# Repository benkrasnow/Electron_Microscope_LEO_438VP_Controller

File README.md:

# LEO 438VP control replacement: working files

Everything generated while reverse-engineering the LEO 438VP SEM's control system: the Win98 PC running LEO-32 plus the custom ISA image-processor board. The analysis tools read the original binaries from an image of the old PC's drive, which is not part of this repository.

Published at https://github.com/benkrasnow/Electron_Microscope_LEO_438VP_Controller. The capture data and the decompiled / disassembled text from the proprietary LEO-32 binaries are kept locally only (see `.gitignore`), so some files mentioned in the docs are not in the repository.

## Layout

| Folder | Contents |
|---|---|
| **`specifications/`** | **Start here: `LEO438VP_SYSTEM_DATASHEET.md` (summary of every subsystem and its architecture).** Detailed interface specs: `STAGE_VACUUM_INTERFACE_SPEC.md`, `VP_CONTROLLER_INTERFACE_SPEC.md`, `EHT_INTERFACE_SPEC.md`, `SCAN_GENERATOR_INTERFACE_SPEC.md` |
| `hardware/leo_control_box/` | KiCad 10 project for the Teensy 4.0 control box (schematic rev 0.1, PCB rev 0.1). See its README |
| **`firmware/`** | **Teensy 4.0 control-box firmware (`leo_control/`), the USB protocol for the PC page (`PROTOCOL.md`) and every runtime setting (`SETTINGS.md`). See `firmware/README.md`** |
| **`webui/`** | **Operator web page (Chrome / Edge): control box over Web Serial, OBI imaging through `bridge.py`, developer tools. See `webui/README.md`** |
| `design/` | Design notes, e.g. the Glasgow pin plan |
| `scope_tools/` | Tektronix MSO24 control and scan-fiber decoding scripts (`arm_burst.py`, `wait_grab_decode.sh`, `decode_scan_fiber.py`, …) and `SCAN_FIBER_NOTES.md` (working notes and test log) |
| `scope_captures/` | The annotated `scan_fiber_timing.png`. The scope captures themselves (`.npz` waveforms, `.png` screens, `_ch3.txt` decodes) are local only |
| `capture_tools/` | Live serial capture: Teensy 3.2 logger firmware, `capture_serial.py`, `decode_serial_log.py`, the protocol write-ups, and every capture. See `capture_tools/README.md`. |
| `capture_tools/captures/` | Raw logs (`<date>_<time>_<tag>.log`), operator notes, decoded timelines and CSVs (local only). |
| `capture_tools/teensy_blink_test/` | Blink sketch used to check the Teensy toolchain. |
| `report/` | The static-analysis report (`leo438vp_report.html`, also published as a claude.ai artifact) plus the section drafts and diagrams it was built from. |
| `analysis/` | Python tools for the original binaries, and their outputs (see below). |
| `notes/` | `PERFORMANCE_TESTS.md` (improvements to try after bring-up), `OLD_SYSTEM_TESTS.md` (checks to run on the old LEO-32 PC) |
| `notes/memory/` | Copy of Claude's project memory (decisions and requirements from the user). |

## Protocol and requirements documents

All in `capture_tools/`:

- `STGVAC_PROTOCOL.md`: stage / vacuum link (UART B, 9600 8N1): polls, pressure conversion, stage counts, thresholds and interlocks.
- `VP_PROTOCOL.md` and `VP_TEST_PLAN.md`: VP controller on PC COM2: hpapp32 commands, states, gauge and setpoint encodings, watchdog.
- `EHT_PROTOCOL.md`: EHT / gun supply link (UART A): commands and encodings, `.O` supply bits, status bits and fault map, ramp sequences, and the VP-mode scintillator behaviour.
- `REPLACEMENT_REQUIREMENTS.md`: rules the new controller must enforce, for example cooling the filament before any pressure change.

## Analysis tools (`analysis/`)

Run them with the original files as arguments, for example `python t34.py "<orig>/TIGA/g100.440" _eht_fault_monitor`.

| Tool | Purpose |
|---|---|
| `coff.py`, `t34.py`, `t340.py` | TI COFF parser and TMS34010/34020 disassembler with relocations and symbols (GSP modules such as `g100.440`) |
| `adsp.py` | Partial ADSP-21xx disassembler (scan-generator DSP code) |
| `ne.py`, `nedis.py`, `mzio.py` | 16-bit NE / MZ executable parsing and disassembly |
| `peinfo.py`, `xref32.py`, `strs.py` | PE32 inspection, string cross-references, string extraction |
| `argtrace.py`, `calls.py`, `cinit.py`, `ext.py`, `movi.py`, `rec.py`, `scanio.py`, `g900map.py` | Call/argument tracing, TIGA extension tables, scan I/O and EO register mapping |
| `syms/` | Symbol dumps of every GSP module (local only) |
| `*_tables.txt`, `*_exports.txt`, `eo_calls.txt` | Extracted TIGA extension tables, exports and EO register call lists (local only) |
| `optics/` | Electron-optics model (`optics_model.py`), fits to the 2026-11-15 captures, emulator driver, Teensy check (`check_teensy.py`). The decompiled `g200.440` listings it was built from are local only |
| `patch8.py`, `patch9.py` | One-off report-editing scripts (historical) |

## Status (2026-11-13)

- Decoded and captured live: stage / vacuum, VP controller and EHT links (serial, Teensy logger).
- Scan-generator fiber link (rev 1.1 spec, incl. beam-on tests: probe current, EHT / kV scaling, Optibeam modes, averaging, board hardware): cold boot, all scan speeds 0-15, magnification sweep with every range, rotation, tilt correction, beam shift, focus / WD / Optibeam / aperture, stigmators, dynamic focus, focus wobble, reduced area / line / spot / external scan, freeze modes. See `specifications/SCAN_GENERATOR_INTERFACE_SPEC.md`.
- Next: design of the replacement IP board. Open items before that: detector video characteristics, F1 / F2 meaning, HRRU, transceiver part numbers (summary datasheet §8).

## How to resume scope captures

1. Scope on the "Ethernet 3" network at 192.168.0.42; probes CH1–CH3 on the IP→EO fibers, CH4 on EO→IP.
2. `cd scope_tools`, then `python scope_setup.py save`.
3. Easiest: run `python cold_boot_loop.py <prefix> [shots] [minutes] [high_limit_us]` in the background; it re-arms after every shot and writes `<prefix>_NN.npz`, `_ch3.txt` and `<prefix>_log.txt` (trigger wall-clock times). `high_limit_us = 2750` catches single writes but only works at scan speed 5 in full frame and not while dynamic focus is on; `100` (default) catches bursts at any speed. About 17 s dead time per shot. Stop it with `touch STOP` in `scope_tools/`.
   Alternative, one shot at a time: `python arm_burst.py`, then `./wait_grab_decode.sh <tag>`, change one control, then `python summarize_burst.py <tag>`.
4. Finish with `python scope_setup.py restore` (if it cannot connect right after the loop stops, retry after ~15 s).

## Version history (git)

This folder is a git repository with the GitHub remote `origin` (see above). Claude commits after each meaningful change so any earlier version can be restored. History was rewritten on 2026-11-15 to drop capture data and decompiled LEO-32 text before publishing; a bundle of the earlier history is in `../Complete_438VP_control_backup_2026-11-15.bundle` (outside the repository). Line-ending conversion is off (`core.autocrlf false`) so KiCad files are stored byte-for-byte.

Useful commands if you ever want them: `git log --oneline` (list versions), `git show <id> --stat` (what changed), `git checkout <id> -- <file>` (restore one file from an earlier version).

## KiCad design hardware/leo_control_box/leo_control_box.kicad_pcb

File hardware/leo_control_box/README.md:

# LEO 438VP control box (KiCad 10 project)

Microcontroller board that owns the SEM's machine state and safety, independent of the PC: EHT, stage/vacuum and VP-controller fiber links, the EO board's four fibers (register link plus the internal-scan backup), a spare I²C expansion port, isolated sync outputs to the OBI, three front-panel pushbutton inputs, an RTC backup cell, a USB-C power input, and a 2×10 IDC header for a 4.3″ 800×480 touch display (Newhaven NHD-4.3-800480FT-CSXP-CTP, FT813 EVE). (PMT signal and gain are handled by separate hardware.) Interface specs: `../../specifications/`.

Status (2026-11-14): **schematic rev 0.1 drawn, ERC clean; PCB placed and autorouted, DRC clean** (0 violations, 0 unconnected, 0 schematic-parity issues). Not yet reviewed by hand or sent for fabrication.

The schematic is generated by `tools/build_schematic.py` (one A2 sheet in functional blocks: power, controller, 6 fiber transmitters, 4 fiber receivers, I²C, isolated OBI sync, display, RTC battery, pushbuttons). Connections are made with net labels and power symbols placed on the pin ends; each MOSFET gate is driven straight from its Teensy pin. **Re-running the script overwrites the schematic**, so either keep editing the script, or switch to hand-editing in KiCad once the circuit is settled (and stop using the script).

## Files

| File | Content |
|---|---|
| `leo_control_box.kicad_pro / .kicad_sch / .kicad_pcb` | project (from KiCad's EuroCard template) |
| `leo_control_box.kicad_sym` | project symbol library (`sym-lib-table`) |
| `leo_control_box.pretty/` | project footprint library (`fp-lib-table`) |
| `tools/build_libs.py` | regenerates both libraries: writes the custom parts, copies the stock ones from the KiCad 10 install (derived symbols flattened) |
| `tools/build_schematic.py` | generates `leo_control_box.kicad_sch` from the netlist in its `build()` function |
| `tools/_pins.py` | helper: reads symbol pin positions |
| `tools/build_pcb.py` | places every footprint from the netlist and assigns nets (`place`), then routes with Freerouting and adds the ground pours (`route`); run with KiCad's Python |
| `pcb_render_top.png` | 3D render of the routed board (top) |
| `leo_control_box_bom.csv` | BOM exported from the schematic (grouped, with Manufacturer, MPN, Digi-Key PN, unit price, notes) |

Passives (R, C, LED, fuse) and generic connectors use KiCad's stock `Device` and `Connector_Generic` symbols; their footprints are in the project library.

## Parts

| Ref | Part | Symbol | Footprint | Source |
|---|---|---|---|---|
| U1 | **Teensy 4.0** | `Teensy_4.0` | `Teensy_4.0` (2 × 14 edge pins, 0.1 in pitch, rows 0.6 in apart) | custom |
| 6× | **HFBR-1521Z** fiber transmitter (EHT, stage/vac, EO F1, F2, F3, VP) | `HFBR-1521Z` | `AGILENT_HFBR-152x` | custom symbol, stock footprint |
| 4× | **HFBR-2521Z** fiber receiver (EHT, stage/vac, EO F4, VP) | `HFBR-2521Z` | `AGILENT_HFBR-252x` | custom symbol, stock footprint |
| 6× | **NX3008NBKVL** logic-level low-side LED switch, one per transmitter, gate driven by the Teensy | `NX3008NBK` (2N7002 drawing, same pinout) | SOT-23 | stock symbol, renamed |
| 2× | Qwiic / STEMMA-QT connector (JST SH 4-pin: GND, 3V3, SDA, SCL) spare I²C expansion | `Conn_01x04_MountingPin` | JST SH SM04B | stock |
| 1× | **ISO6720FBDR** 2-channel digital isolator for the OBI sync outputs | `ISO6720FBD` | SOIC-8 | stock |
| 1× | OBI sync header J6: Vio (from the OBI), LINE_SYNC, FRAME_SYNC, SYNC_GND (isolated) | `Conn_01x04` | 1 × 4 2.54 mm | stock |
| 1× | Pushbutton header J11: BTN1, BTN2, BTN3, GND | `Conn_01x04` | 1 × 4 2.54 mm | stock |
| off-board | 3 panel pushbuttons, E-Switch PS1024AL (1 red, 2 black), wired to J11 | `MountingHole` placeholders X3–X5 | — | — |
| 1× | **CR2032 cell with solder tabs** (Panasonic CR-2032/HFN) for the Teensy RTC, plus TP1 wire pad | `Battery_Cell`, `TestPoint` | Battery_Panasonic_CR2032-HFN_Horizontal, TestPoint THT 1.5 mm | stock |
| 1× | Display header, 2×10 shrouded box header (Sullins SBH11-PBPC-D10-ST-BK) | `Conn_02x10_Odd_Even` | IDC-Header_2x10_P2.54mm_Vertical | stock |
| off-board | Newhaven NHD-4.3-800480FT-CSXP-CTP display + Adafruit 5294 2×10 IDC cable (1 ft) | `MountingHole` placeholders X1/X2, in BOM, not on the board | — | — |
| 1× | **USB-C power-only receptacle** (GCT USB4125-GF-A) with 5.1 kΩ CC pull-downs R65/R66: 5 V from a plain wall adapter, no USB data or PD | `USB_C_Receptacle_PowerOnly_6P` | USB_C_Receptacle_GCT_USB4125-xx-x_6P_TopMnt_Horizontal | stock |
| 1× | 1812 PTC fuse + bulk capacitor | `Polyfuse`, `C` | Fuse 1812, C 1206 | stock |
| — | R / C / LED 0805 | `R`, `C`, `LED` | 0805 | stock |

No DAC, ADC or knob on this board (removed 2026-11-14: the PMT amplifier and its gain are handled by separate hardware; a focus knob was not chosen).

## Teensy 4.0 vs 4.1

The 4.0 works. It has everything this board needs on its 24 edge I/O pins: 7 hardware UARTs (we use 3), FlexIO1 on pins 2–5 for the EO frames, I²C on 18/19; all 24 edge pins are now used. It lacks the 4.1's Ethernet, so the PC link is USB. **Cut the Teensy's VUSB–VIN pad before fitting it.** The board's 5 V (from USB-C J10) feeds VIN; with the pad intact that 5 V would also drive the PC's USB port, and the PC could power the board. Cut, the PC link carries data only, so plugging or resetting the PC cannot reset the controller (the Teensy does not reset when a serial port is opened). Use a 4.1 only if Ethernet isolation from the PC becomes a requirement.

Teensy 4.x pins are **3.3 V only (not 5 V tolerant)**: every 5 V signal must be level-shifted (see the receivers below).

## Planned Teensy pin use (verify FlexIO assignments against the PJRC pinout before layout)

| Pin | Function | Connects to |
|---|---|---|
| 0 / 1 | Serial1 RX / TX | EHT fiber RX / TX |
| 7 / 8 | Serial2 RX / TX | Stage/vacuum fiber RX / TX |
| 15 / 14 | Serial3 RX / TX | VP controller fiber RX / TX (its RX1/TX1 port) |
| 2 | FlexIO1 out | EO F3 register frames (3.6864 Mbit/s) |
| 3 | FlexIO1 in | EO F4 read replies |
| 4 | timer / GPIO | EO F1 frame gate (internal-scan backup) |
| 5 | timer / GPIO | EO F2 line gate (internal-scan backup) |
| 6, 9 | GPIO out | ISO6720 inputs → isolated LINE_SYNC, FRAME_SYNC on J6 (56 Ω series on the isolated side) |
| 18 / 19 | I²C SDA / SCL (2.2 kΩ to 3.3 V) | Qwiic expansion connectors J3 / J4 |
| 23 | GPIO out | status LED |
| 10 / 11 / 12 / 13 | SPI CS / MOSI / MISO / SCK | display J9 (CS 10k pull-up; SCK and MOSI through 56 Ω series resistors) |
| 21 | GPIO out | display /PD (10k pull-down: off until enabled) |
| 22 | GPIO in | display /INT (10k pull-up) |
| 16, 17, 20 | GPIO in (active low) | pushbuttons 1 (red, safe state), 2, 3 via J11 |

## Circuit notes

**Fiber transmitter channel (×6).**
Teensy pin → NX3008NBK gate (direct; no buffer) → HFBR-1521Z cathode. The NX3008NBK (Nexperia, 30 V) has V_GS(th) ≤ 1.1 V, R_DS(on) specified down to 1.8 V gate drive, and C_iss ≤ 50 pF, so a 3.3 V Teensy pin turns it fully on and switches it in a few ns. (Until 2026-11-14 this was a 74AHCT125 buffer driving a 2N7002 at 5 V, because a 2N7002 is not guaranteed to turn on fully at 3.3 V.) The anode goes through a current-setting resistor to +5 V (≈ 56 Ω for ~55 mA; set from the datasheet's recommended drive for 5 MBd). Add a footprint for the datasheet's peaking capacitor across the resistor.
- Logic high = LED on = line idle, which matches all links (idle high).
- **10 kΩ pull-up to 3.3 V on each gate**, so the lines idle high (no false start bits) while the Teensy is in reset or being programmed.

**Fiber receiver channel (×4).**
HFBR-2521Z VCC from +5 V, with the decoupling/filter network recommended in the datasheet. VO is an open-collector output: pull it up to **3.3 V** (1 kΩ) and connect it straight to the Teensy pin, leaving RL (the internal 5 V load resistor) unconnected. That keeps the Teensy pin at a safe 3.3 V level. Check the rise time against the 271 ns EO bit period on the first board (~15 pF × 1 kΩ ≈ 15 ns, fine).

**VP controller link (fiber, replaced RS-232 on 2026-11-14).**
The VP control board (98/46) has an unused Versatile Link fiber port (TX1 HFBR-1524, RX1 HFBR-2524) wired, through its 4-way DIP switch, to the same MC68HC705C8 SCI pins as its DE-9. Set its switches 2 and 4 ON and 1 and 3 OFF (1 = brown, TX to RS-232; 2 = red, TX to fiber; 3 = orange, RX from RS-232; 4 = yellow, RX from fiber); never 3 and 4 together. Same 9600 8N1 protocol as before (`specifications/VP_CONTROLLER_INTERFACE_SPEC.md`). With this, every connection from the box to the SEM is fiber.
- Still to confirm on the VP board: idle polarity of its fiber port (is TX1 lit at idle?) and the RX1 path (that trace is on the top layer).
- Our channel uses an HFBR-1521Z / HFBR-2521Z like the others. Their 1524/2524 pair is the slower, high-sensitivity grade: with 55 mA into our transmitter their receiver may be overdriven. If the link is marginal, raise R25 (less LED current) or fit an HFBR-1524/2524 pair here (same footprints).

**I²C.**
3.3 V bus with 2.2 kΩ pull-ups on two Qwiic sockets, kept as a spare expansion port (no devices on board).

**OBI sync (isolated).**
Teensy 6/9 → ISO6720FBDR side 1 (+3V3, board GND) → side 2 → 56 Ω → J6. Side 2 is powered from the OBI end through J6 pin 1 (the Glasgow port's Vio, 1.8–5 V; the isolator draws a few mA) and its ground is SYNC_GND, which must stay separate from board GND in layout (keep the isolation gap under U13 clear of copper). This breaks the ground loop PC → USB → Teensy → sync cable → OBI → USB → PC. The F variant's outputs default low when side 1 is unpowered, so a powered-down box sends no sync edges.

**Pushbuttons.**
Three panel buttons on J11 (button to GND). Each input has a 10 kΩ pull-up and 100 nF to GND at the header (≈1 ms release RC) and a 1 kΩ series resistor to the Teensy pin. Button 1 (red) is intended as the safe-state button (EHT and filament off, following the filament-off rule); 2 and 3 are unassigned. Debounce in firmware as well.

**RTC backup.**
BT1 (CR2032 with solder tabs) keeps the Teensy's real-time clock running while the box is off, so log entries carry real timestamps. The Teensy 4.0's VBAT is a pad on its underside, so run a short wire from TP1 to that pad. The cell is only drawn on while the board is unpowered.

**Power.**
5 V from the USB-C receptacle J10 (the only supply input) → PTC fuse → +5 V rail (HFBR parts, Teensy VIN). The Teensy's 3.3 V regulator feeds the isolator, the display logic and the pull-ups (it can supply ~250 mA).

## Before layout: verify against datasheets

- HFBR-1521Z / HFBR-2521Z pin numbering (symbol pins 1–4; pads 5/6 are the mounting posts), the recommended LED drive current and peaking network, and the receiver filter network (Broadcom AV02-3283EN / AV02-1501EN).
- Teensy 4.0 footprint dimensions against the PJRC drawing (pad 1 = GND at the USB end; right row from the far end: 13 … 23, 3V3, GND, VIN), and the FlexIO pin assignments.

## Schematic reference designators

| Block | Refs |
|---|---|
| Power | J10 (5 V in, USB-C) with R65/R66 5.1 kΩ CC pull-downs, F1, C1, C2, D1/R1 power LED, D2/R2 status LED (Teensy 23) |
| Controller | U1 Teensy 4.0 |
| Fiber TX (EHT, STG, EO F1, F2, F3, VP) | R10–R15 gate pull-ups, Q1–Q6 NX3008NBK, U4–U8 and U12 HFBR-1521Z, R20–R25 LED current (56 Ω), C20–C25 peaking (DNP) |
| Fiber RX (EHT, STG, EO F4, VP) | U9–U11 and U14 HFBR-2521Z, C40–C43, R30–R33 pull-ups (1 k to 3.3 V) |
| I²C expansion | R40/R41 SDA/SCL pull-ups (2.2 k), J3/J4 Qwiic |
| OBI sync | U13 ISO6720FBDR, C70/C71, R50/R51 (56 Ω, same part as the LED resistors), J6 |
| RTC | BT1 CR2032, TP1 (wire to Teensy VBAT) |
| Pushbuttons | J11, R70–R72 pull-ups (10k), C72–C74 (100n), R73–R75 series (1k); off-board X3–X5 |

Values to confirm before ordering: LED current resistors R20–R25 and the peaking caps (HFBR-1521Z datasheet), and F1 rating.

## Purchasing (Digi-Key, checked 2026-11-13)

Every part carries `Manufacturer`, `MPN`, `DigiKey_PN`, `Unit_Price_USD` and `BOM_Note` fields (set in `PARTS` in `tools/build_schematic.py`); export with `kicad-cli sch export bom` (see `leo_control_box_bom.csv`). Rules applied: in stock at Digi-Key, not Marketplace, orderable in single quantities (cut tape where offered); values consolidated.

- **To buy: about $14.93** for the board at single-quantity prices, plus **$82.17** off-board (display, cable, 3 pushbuttons). History: $13.82 after removing the DAC/ADC/knob, then the display header, USB-C input, isolator, RTC cell and button inputs (2026-11-14); terminal block J1 removed; MAX3232 and DE-9 replaced by a sixth fiber transmitter and fourth receiver (VP link); 74AHCT125 buffers removed and 2N7002 replaced by NX3008NBKVL.
- **Already in stock with the owner:** Teensy 4.0 (Digi-Key stock 0), HFBR-1521Z ×6 (Digi-Key backordered; in-stock alternative AFBR-1521CZ, 516-3584-ND, 30 mA max drive), HFBR-2521Z ×4.
- **Substitutions:** Bourns MF-MSMF110-2 (obsolete) → **Littelfuse 1812L110/16DR** (1.1 A hold, 16 V, 1812).
- **Consolidation:** four resistor values (10k, 1k, 2.2k, 56 Ω; the sync series resistors moved from 33 to 56 Ω); one 100 nF part for all 11 decoupling/debounce capacitors; one green LED for both indicators; one 1 × 40 header strip, cut for J6 and J11.
- Peaking capacitors C20–C25 are DNP (no part chosen).

## Touch display (added 2026-11-14)

Newhaven **NHD-4.3-800480FT-CSXP-CTP**: 4.3″ 800×480 IPS, capacitive touch, FT813 EVE controller, SPI up to 30 MHz (datasheet rev 8, 09/16/2026). It connects through its 2×10 2.54 mm IDC box header (CN1) and a straight-through 20-way ribbon to J9 on this board.

| J9 / CN1 pin | Signal | Connection |
|---|---|---|
| 1 | VDD (3.0–3.5 V, 40 mA) | +3V3 (Teensy regulator) |
| 2, 19, 20 | GND | GND |
| 3 | SCK | Teensy 13 via R60 56 Ω |
| 4 | MISO / IO1 | Teensy 12 |
| 5 | MOSI / IO0 | Teensy 11 via R61 56 Ω |
| 6 | /CS | Teensy 10, R62 10k pull-up |
| 7 | /INT | Teensy 22, R63 10k pull-up |
| 8 | /PD | Teensy 21, R64 10k pull-down |
| 9 | AUDIO_L (PWM) | not used |
| 10, 15, 16 | NC | — |
| 11–14 | GPIO0–3 (IO2/IO3 for quad SPI) | not used (single-SPI mode) |
| 17, 18 | VBL backlight (2.8–5.5 V; 240 mA at 5 V, 520 mA at 3.3 V) | +5V |

Decoupling at J9: C62 100 nF (+3V3), C63 47 µF (+5V). Estimated +5V load with the display: Teensy ~100 mA + six transmitter LEDs ~330 mA (lit while idle) + receivers and logic ~50 mA + backlight 240 mA ≈ 0.72 A, within F1's 1.1 A hold rating. The +3V3 rail (Teensy regulator) gains 40 mA.

Costs: see Purchasing above.

## USB-C power input (added 2026-11-14)

J10 is a power-only USB-C receptacle (GCT USB4125-GF-A, 2073-USB4125-GF-ACT-ND, $0.61). VBUS goes to +5V_IN, ahead of the PTC fuse (the terminal block J1 was removed: USB-C is the only input); the shield and GND go to ground. CC1 and CC2 each have a 5.1 kΩ pull-down (R65, R66), which identifies the board as a USB sink, so USB-C-to-C chargers switch on their 5 V output. USB-A wall adapters with an A-to-C cable supply 5 V regardless.

- No PD controller: the board only ever gets 5 V. It does not read the charger's advertised current (Default / 1.5 A / 3 A), so use an adapter rated **at least 1.5 A** (the board draws about 0.72 A with the display).

## PCB (rev 0.1, placed and autorouted 2026-11-14)

160 × 100 mm, 2 layers (the KiCad EuroCard template outline), four M2.5 corner holes. 

- **Top edge:** the ten fiber connectors, noses at the board edge, left to right: EHT TX, EHT RX, STG TX, STG RX, VP TX, VP RX, EO F1, EO F2, EO F3, EO F4. Each channel's resistor / MOSFET / capacitor sits directly below its connector, with a silkscreen label. (The routed board predates the 2026-11-14 driver change; see below.)
- **Right edge:** Teensy 4.0 with its USB toward the edge (silkscreen "CUT VUSB-VIN"), USB-C power J10 below it with the fuse, bulk capacitors and LEDs.
- **Bottom edge:** display header J9, button header J11, and the isolated OBI sync corner (J6, U13). That corner has its own SYNC_GND pour; the board GND pour stops at the split under U13.
- **Left edge:** the two Qwiic sockets, facing out.
- CR2032 holder BT1 in the middle; TP1 next to the Teensy for the VBAT wire.

Routing: Freerouting 1.9.0 (`tools/freerouting/`, not in git; run `python tools/build_pcb.py route` with KiCad's Python). Track widths: 0.25 mm default, 0.5 mm for +5V, +5V_IN and GND (net class "Power"). GND pours on both layers, solid pad connections.

How to rebuild after a schematic change: `python tools/build_schematic.py`, export the netlist (`kicad-cli sch export netlist --format kicadsexpr -o leo_control_box.net leo_control_box.kicad_sch`), then `build_pcb.py place` and `build_pcb.py route` (KiCad's Python). Symbol UUIDs are derived from the reference designators, so the PCB stays linked to the schematic. **Once you start editing the board by hand in KiCad, stop re-running `place`/`route`** (they rebuild the board from scratch); use KiCad's "Update PCB from Schematic" instead.

Before ordering, review in KiCad:
- Autorouted traces are functional, not pretty: check the 3.7 Mbit/s EO lines (EO_F3 and EO_F4 to the Teensy) and tidy any long detours.
- Fiber connector positions against the enclosure panel, and the Teensy USB / USB-C positions against their cut-outs.
- Solid pad-to-pour connections make the THT ground pins slower to solder; switch the pours to thermal relief if preferred.
- The HFBR pinout and footprint (see "Before layout: verify against datasheets").

### Schematic changed after the hand-edited layout (2026-11-14)

The transmitters lost their 74AHCT125 buffers: U2, U3, C30 and C31 are gone, Q1–Q6 are now NX3008NBK (same SOT-23 footprint and pinout), and each gate net is now the Teensy signal itself (EHT_TX, STG_TX, VP_TX, EO_F1, EO_F2, EO_F3) instead of a separate buffer-output net. **The PCB was deliberately not touched** (it has hand edits). To bring it in line: open the board in KiCad and run Tools → Update PCB from Schematic. It will delete U2, U3, C30 and C31 and reassign the Q gate pads to the Teensy nets. The tracks that went to the old buffers stay behind as dangling copper: delete them, then route the six gate connections by hand (Teensy pin → gate; the 10k pull-ups are already on those nets). Do not run `tools/build_pcb.py`, which rebuilds the board from scratch.

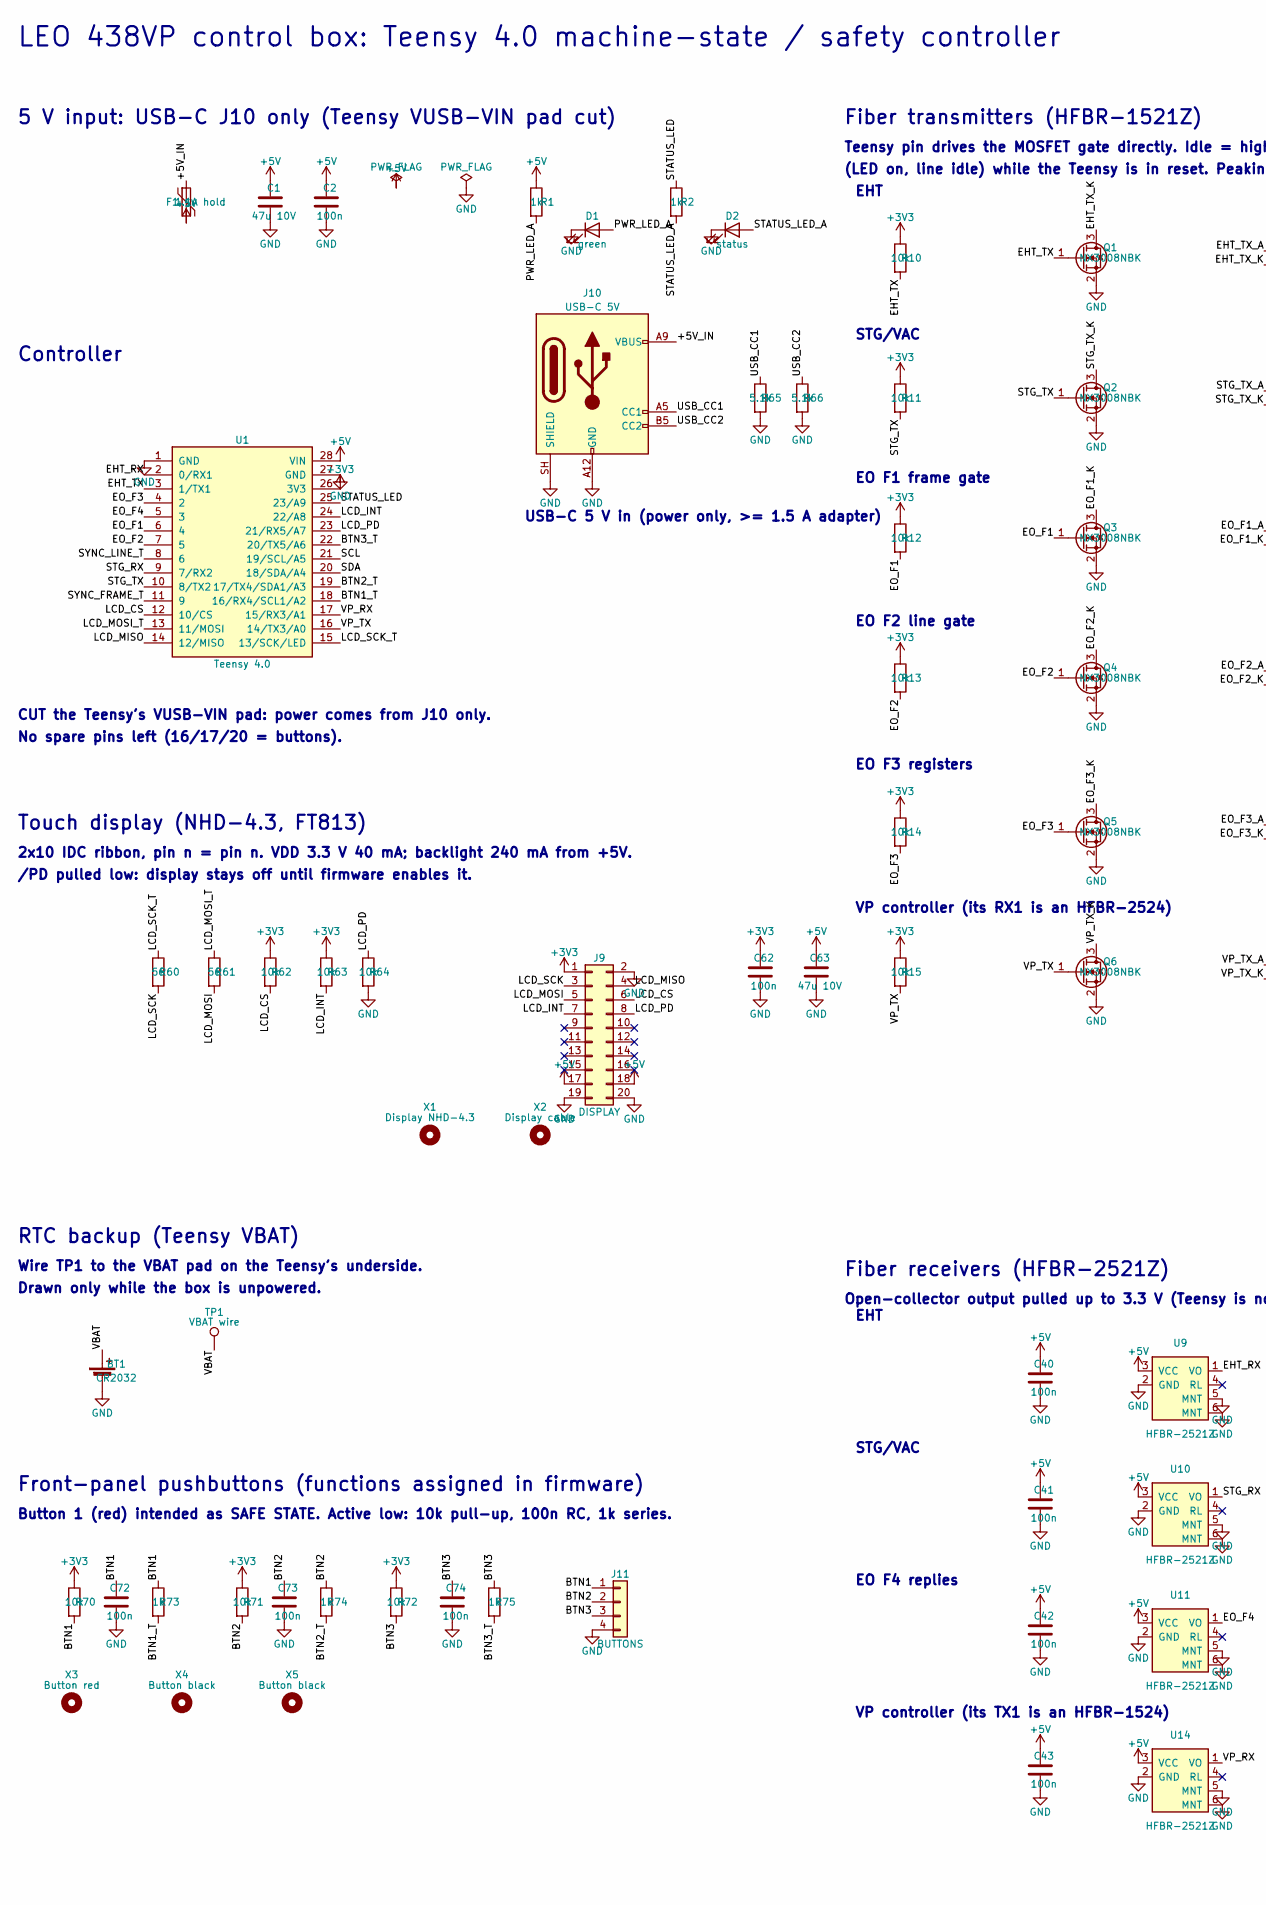
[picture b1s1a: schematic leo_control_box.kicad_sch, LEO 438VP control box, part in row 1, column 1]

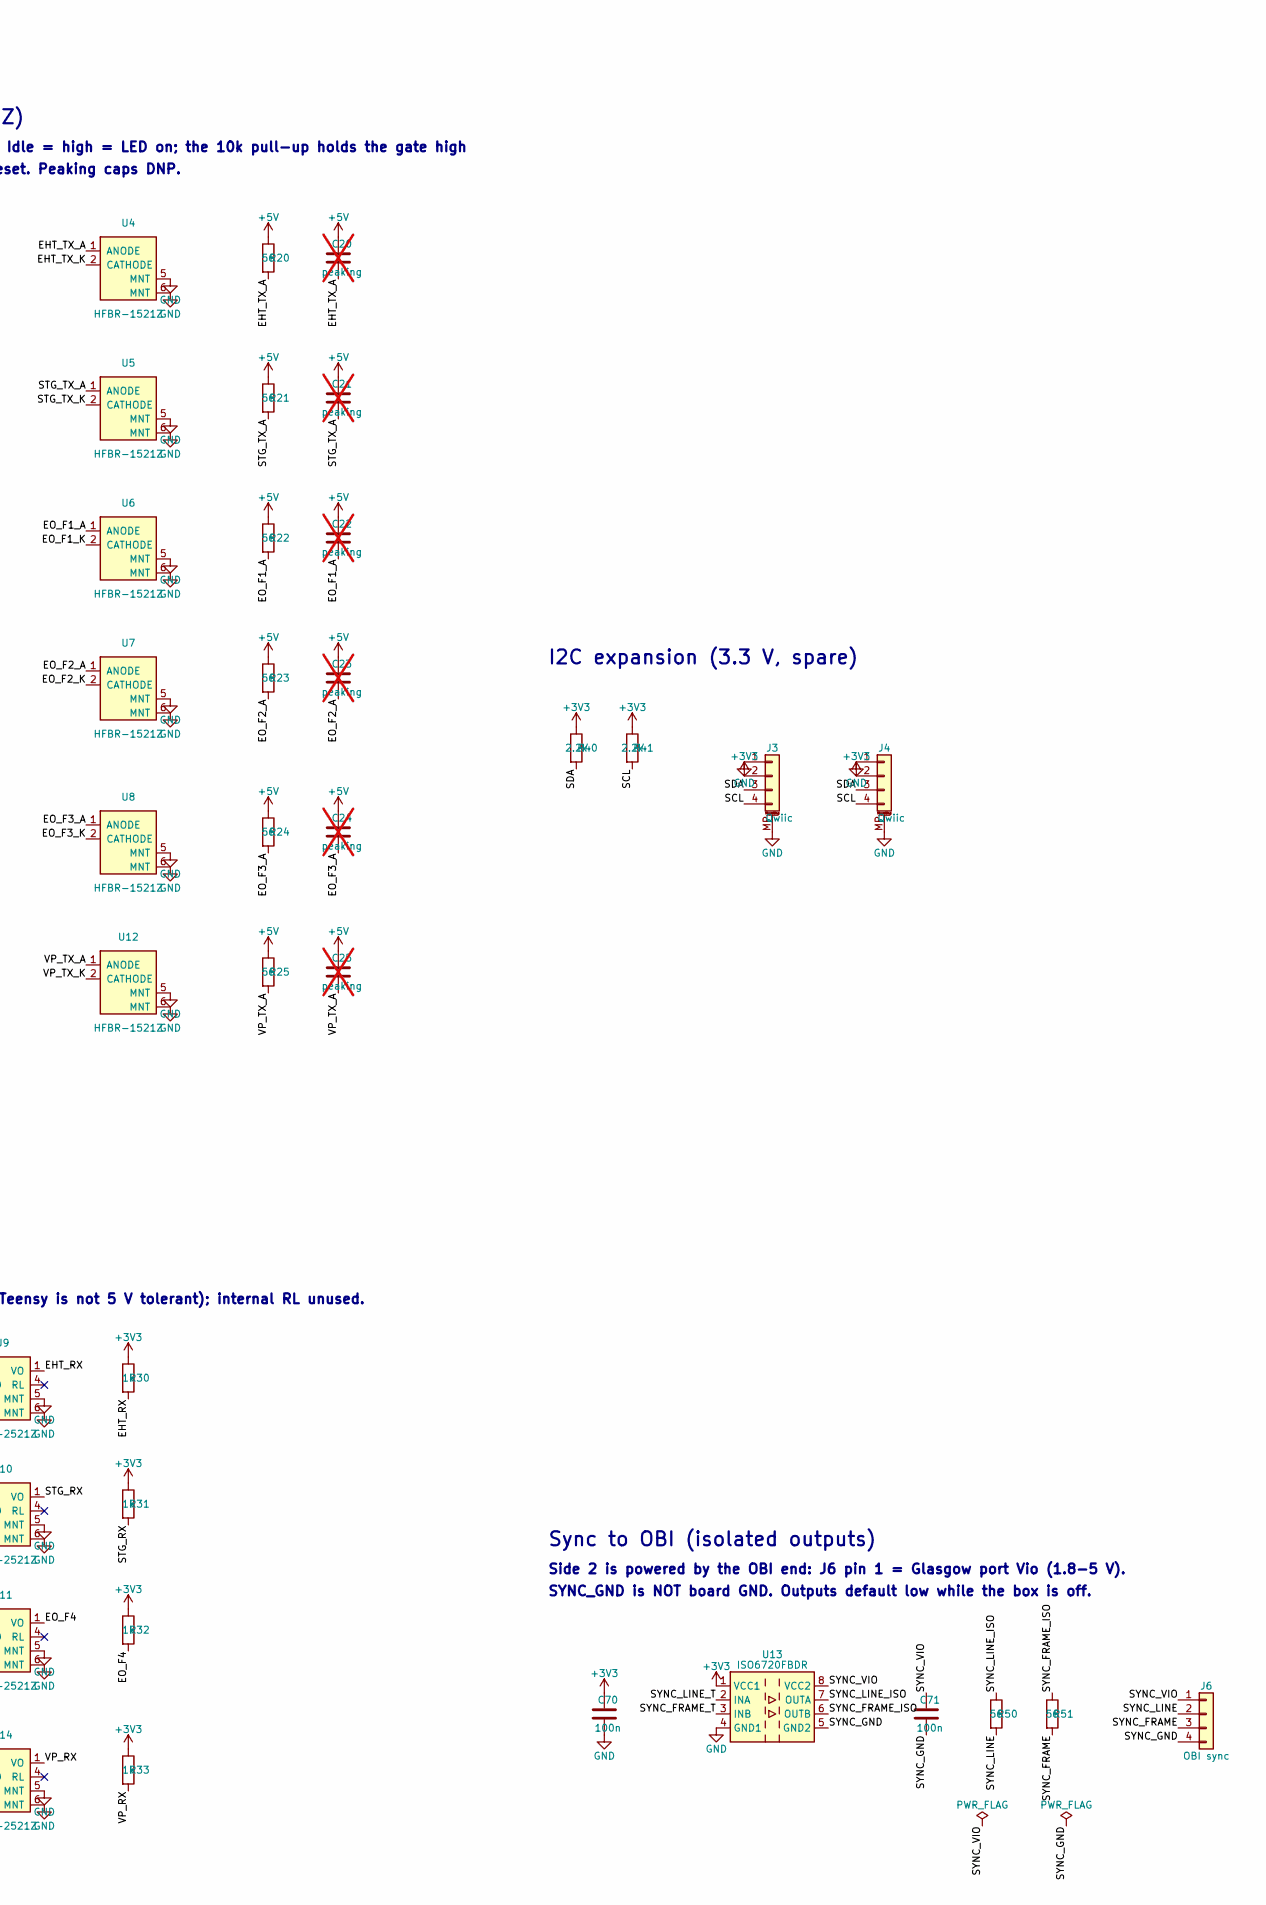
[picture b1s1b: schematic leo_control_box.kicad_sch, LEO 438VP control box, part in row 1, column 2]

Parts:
BT1: CR2032; Battery_Panasonic_CR2032-HFN_Horizontal_CircularHoles; MPN CR-2032/HFN; DigiKey_PN 11-CR-2032/HFN-ND
C1, C63: 47u 10V; C_1206_3216Metric; MPN CL31A476MPHNNNE; DigiKey_PN 1276-3063-1-ND
C2, C40, C41, C42, C43, C62, C70, C71, C72, C73, C74: 100n; C_0805_2012Metric; MPN CL21B104KBCNNNC; DigiKey_PN 1276-1003-1-ND
C20, C21, C22, C23, C24, C25: peaking; C_0805_2012Metric; not fitted
D1: green; LED_0805_2012Metric; MPN LTST-C171GKT; DigiKey_PN 160-1423-1-ND
D2: status; LED_0805_2012Metric; MPN LTST-C171GKT; DigiKey_PN 160-1423-1-ND
F1: 1.1A hold; Fuse_1812_4532Metric; MPN 1812L110/16DR; DigiKey_PN F3485CT-ND
J3, J4: Qwiic; JST_SH_SM04B-SRSS-TB_1x04-1MP_P1.00mm_Horizontal; MPN SM04B-SRSS-TB(LF)(SN); DigiKey_PN 455-SM04B-SRSS-TBCT-ND
J6: OBI sync; PinHeader_1x04_P2.54mm_Vertical; MPN PRPC040SAAN-RC; DigiKey_PN S1011EC-40-ND
J9: DISPLAY; IDC-Header_2x10_P2.54mm_Vertical; MPN SBH11-PBPC-D10-ST-BK; DigiKey_PN S9172-ND
J10: USB-C 5V; USB_C_Receptacle_GCT_USB4125-xx-x_6P_TopMnt_Horizontal; MPN USB4125-GF-A; DigiKey_PN 2073-USB4125-GF-ACT-ND
J11: BUTTONS; PinHeader_1x04_P2.54mm_Vertical; MPN PRPC040SAAN-RC; DigiKey_PN S1011EC-40-ND
Q1, Q2, Q3, Q4, Q5, Q6: NX3008NBK; SOT-23; MPN NX3008NBKVL; DigiKey_PN 1727-NX3008NBKVLCT-ND
R1, R2, R30, R31, R32, R33, R73, R74, R75: 1k; R_0805_2012Metric; MPN RC0805FR-071KL; DigiKey_PN 311-1.00KCRCT-ND
R10, R11, R12, R13, R14, R15, R62, R63, R64, R70, R71, R72: 10k; R_0805_2012Metric; MPN RC0805FR-0710KL; DigiKey_PN 311-10.0KCRCT-ND
R20, R21, R22, R23, R24, R25, R50, R51, R60, R61: 56; R_0805_2012Metric; MPN RC0805FR-0756RL; DigiKey_PN 311-56.0CRCT-ND
R40, R41: 2.2k; R_0805_2012Metric; MPN RC0805FR-072K2L; DigiKey_PN 311-2.20KCRCT-ND
R65, R66: 5.1k; R_0805_2012Metric; MPN RC0805FR-075K1L; DigiKey_PN 311-5.10KCRCT-ND
TP1: VBAT wire; TestPoint_THTPad_D1.5mm_Drill0.7mm
U1: Teensy 4.0; Teensy_4.0; MPN 15583 (Teensy 4.0); DigiKey_PN 1568-15583-ND
U4, U5, U6, U7, U8, U12: HFBR-1521Z; AGILENT_HFBR-152x; MPN HFBR-1521Z; DigiKey_PN 516-2043-ND
U9, U10, U11, U14: HFBR-2521Z; AGILENT_HFBR-252x; MPN HFBR-2521Z; DigiKey_PN 516-2062-ND
U13: ISO6720FBDR; SOIC-8_3.9x4.9mm_P1.27mm; MPN ISO6720FBDR; DigiKey_PN 296-ISO6720FBDRCT-ND
X1: Display NHD-4.3; MPN NHD-4.3-800480FT-CSXP-CTP; DigiKey_PN 757-NHD-4.3-800480FT-CSXP-CTP-ND
X2: Display cable; MPN 5294; DigiKey_PN 1528-5294-ND
X3: Button red; MPN PS1024ALRED; DigiKey_PN EG2025-ND
X4, X5: Button black; MPN PS1024ALBLK; DigiKey_PN EG2021-ND

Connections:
+3V3: C62.1, C70.1, J3.2, J4.2, J9.1, R10.1, R11.1, R12.1, R13.1, R14.1, R15.1, R30.1, R31.1, R32.1, R33.1, R40.1, R41.1, R62.1, R63.1, R70.1, R71.1, R72.1, U1.26 (3V3), U13.1 (VCC1)
+5V: C1.1, C2.1, C20.1, C21.1, C22.1, C23.1, C24.1, C25.1, C40.1, C41.1, C42.1, C43.1, C63.1, F1.2, J9.17, J9.18, R1.1, R20.1, R21.1, R22.1, R23.1, R24.1, R25.1, U1.28 (VIN), U9.3 (VCC), U10.3 (VCC), U11.3 (VCC), U14.3 (VCC)
/+5V_IN: F1.1, J10.A9 (VBUS), J10.B9 (VBUS)
/BTN1: C72.1, J11.1, R70.2, R73.1
/BTN1_T: R73.2, U1.18 (16/RX4/SCL1/A2)
/BTN2: C73.1, J11.2, R71.2, R74.1
/BTN2_T: R74.2, U1.19 (17/TX4/SDA1/A3)
/BTN3: C74.1, J11.3, R72.2, R75.1
/BTN3_T: R75.2, U1.22 (20/TX5/A6)
/EHT_RX: R30.2, U1.2 (0/RX1), U9.1 (VO)
/EHT_TX: Q1.1 (G), R10.2, U1.3 (1/TX1)
/EHT_TX_A: C20.2, R20.2, U4.1 (ANODE)
/EHT_TX_K: Q1.3 (D), U4.2 (CATHODE)
/EO_F1: Q3.1 (G), R12.2, U1.6 (4)
/EO_F1_A: C22.2, R22.2, U6.1 (ANODE)
/EO_F1_K: Q3.3 (D), U6.2 (CATHODE)
/EO_F2: Q4.1 (G), R13.2, U1.7 (5)
/EO_F2_A: C23.2, R23.2, U7.1 (ANODE)
/EO_F2_K: Q4.3 (D), U7.2 (CATHODE)
/EO_F3: Q5.1 (G), R14.2, U1.4 (2)
/EO_F3_A: C24.2, R24.2, U8.1 (ANODE)
/EO_F3_K: Q5.3 (D), U8.2 (CATHODE)
/EO_F4: R32.2, U1.5 (3), U11.1 (VO)
/LCD_CS: J9.6, R62.2, U1.12 (10/CS)
/LCD_INT: J9.7, R63.2, U1.24 (22/A8)
/LCD_MISO: J9.4, U1.14 (12/MISO)
/LCD_MOSI: J9.5, R61.2
/LCD_MOSI_T: R61.1, U1.13 (11/MOSI)
/LCD_PD: J9.8, R64.1, U1.23 (21/RX5/A7)
/LCD_SCK: J9.3, R60.2
/LCD_SCK_T: R60.1, U1.15 (13/SCK/LED)
/PWR_LED_A: D1.2 (A), R1.2; also elsewhere on the board
/SCL: J3.4, J4.4, R41.2, U1.21 (19/SCL/A5)
/SDA: J3.3, J4.3, R40.2, U1.20 (18/SDA/A4)
/STATUS_LED: R2.1, U1.25 (23/A9)
/STATUS_LED_A: D2.2 (A), R2.2; also elsewhere on the board
/STG_RX: R31.2, U1.9 (7/RX2), U10.1 (VO)
/STG_TX: Q2.1 (G), R11.2, U1.10 (8/TX2)
/STG_TX_A: C21.2, R21.2, U5.1 (ANODE)
/STG_TX_K: Q2.3 (D), U5.2 (CATHODE)
/SYNC_FRAME: J6.3, R51.2
/SYNC_FRAME_ISO: R51.1, U13.6 (OUTB)
/SYNC_FRAME_T: U1.11 (9), U13.3 (INB)
/SYNC_GND: C71.2, J6.4, U13.5 (GND2)
/SYNC_LINE: J6.2, R50.2
/SYNC_LINE_ISO: R50.1, U13.7 (OUTA)
/SYNC_LINE_T: U1.8 (6), U13.2 (INA)
/SYNC_VIO: C71.1, J6.1, U13.8 (VCC2)
/USB_CC1: J10.A5 (CC1), R65.1
/USB_CC2: J10.B5 (CC2), R66.1
/VBAT: BT1.1 (+), TP1.1; also elsewhere on the board
/VP_RX: R33.2, U1.17 (15/RX3/A1), U14.1 (VO)
/VP_TX: Q6.1 (G), R15.2, U1.16 (14/TX3/A0)
/VP_TX_A: C25.2, R25.2, U12.1 (ANODE)
/VP_TX_K: Q6.3 (D), U12.2 (CATHODE)
GND: BT1.2 (-), C1.2, C2.2, C40.2, C41.2, C42.2, C43.2, C62.2, C63.2, C70.2, C72.2, C73.2, C74.2, D1.1 (K), D2.1 (K), J3.1, J3.MP (MountPin), J4.1, J4.MP (MountPin), J9.2, J9.19, J9.20, J10.A12 (GND), J10.B12 (GND), J10.SH (SHIELD), J11.4, Q1.2 (S), Q2.2 (S), Q3.2 (S), Q4.2 (S), Q5.2 (S), Q6.2 (S), R64.2, R65.2, R66.2, U1.1 (GND), U1.27 (GND), U4.5 (MNT), U4.6 (MNT), U5.5 (MNT), U5.6 (MNT), U6.5 (MNT), U6.6 (MNT), U7.5 (MNT), U7.6 (MNT), U8.5 (MNT), U8.6 (MNT), U9.2 (GND), U9.5 (MNT), U9.6 (MNT), U10.2 (GND), U10.5 (MNT), U10.6 (MNT), U11.2 (GND), U11.5 (MNT), U11.6 (MNT), U12.5 (MNT), U12.6 (MNT), U13.4 (GND1), U14.2 (GND), U14.5 (MNT), U14.6 (MNT); also elsewhere on the board

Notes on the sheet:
Wire TP1 to the VBAT pad on the Teensy's underside.
Side 2 is powered by the OBI end: J6 pin 1 = Glasgow port Vio (1.8-5 V).
Sync to OBI (isolated outputs)
Button 1 (red) intended as SAFE STATE. Active low: 10k pull-up, 100n RC, 1k series.
EO F2 line gate
I2C expansion (3.3 V, spare)
Drawn only while the box is unpowered.
5 V input: USB-C J10 only (Teensy VUSB-VIN pad cut)
SYNC_GND is NOT board GND. Outputs default low while the box is off.
VP controller (its TX1 is an HFBR-1524)
Front-panel pushbuttons (functions assigned in firmware)
STG/VAC
2x10 IDC ribbon, pin n = pin n. VDD 3.3 V 40 mA; backlight 240 mA from +5V.
No spare pins left (16/17/20 = buttons).
CUT the Teensy's VUSB-VIN pad: power comes from J10 only.
EO F3 registers
Touch display (NHD-4.3, FT813)
Fiber transmitters (HFBR-1521Z)
/PD pulled low: display stays off until firmware enables it.
EO F1 frame gate
USB-C 5 V in (power only, >= 1.5 A adapter)
(LED on, line idle) while the Teensy is in reset. Peaking caps DNP.
Fiber receivers (HFBR-2521Z)
Controller
Open-collector output pulled up to 3.3 V (Teensy is not 5 V tolerant); internal RL unused.
EHT
LEO 438VP control box: Teensy 4.0 machine-state / safety controller
VP controller (its RX1 is an HFBR-2524)
EO F4 replies
Teensy pin drives the MOSFET gate directly. Idle = high = LED on; the 10k pull-up holds the gate high
RTC backup (Teensy VBAT)

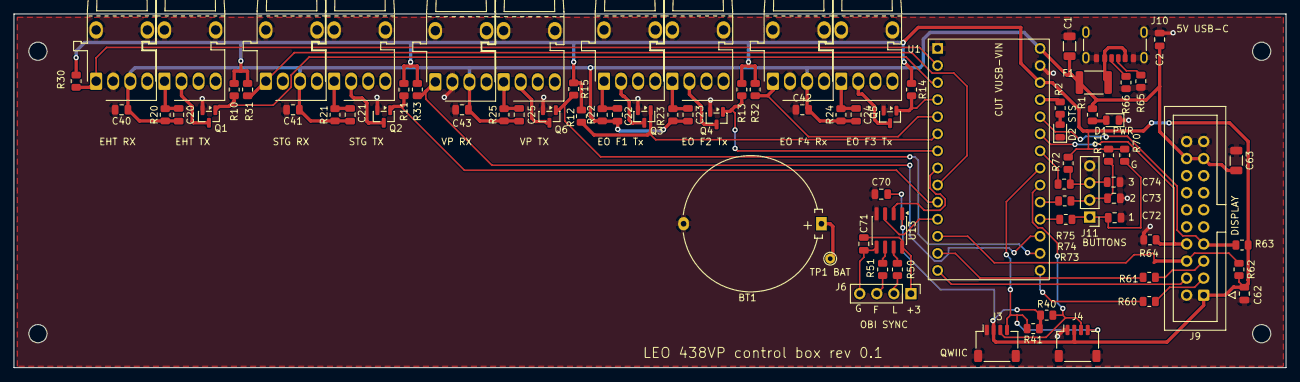
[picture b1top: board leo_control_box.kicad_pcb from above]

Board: 2 copper layers, 189.2 x 52.6 mm, 87 parts (0 on the bottom side), 56 nets.

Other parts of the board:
D1 PWR: green; LED_0805_2012Metric
D2 STS: status; LED_0805_2012Metric
MH1, MH2, MH3, MH4: MountingHole_2.7mm_M2.5_DIN965
TP1 BAT: VBAT wire; TestPoint_THTPad_D1.5mm_Drill0.7mm

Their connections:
/PWR_LED_A: D1 PWR.2 (A); also elsewhere on the board
/STATUS_LED_A: D2 STS.2 (A); also elsewhere on the board
/VBAT: TP1 BAT.1 (1_1); also elsewhere on the board
GND: D1 PWR.1 (K), D2 STS.1 (K); also elsewhere on the board

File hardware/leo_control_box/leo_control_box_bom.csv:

"Refs","Value","Footprint","Manufacturer","MPN","DigiKey PN","Unit price (USD)","Qty","Note","DNP"
"BT1","CR2032","leo_control_box:Battery_Panasonic_CR2032-HFN_Horizontal_CircularHoles","Panasonic","CR-2032/HFN","11-CR-2032/HFN-ND","1.40","1","CR2032 with solder tabs, Teensy RTC backup",""
"C1,C63","47u 10V","leo_control_box:C_1206_3216Metric","Samsung Electro-Mechanics","CL31A476MPHNNNE","1276-3063-1-ND","0.59","2","10 V X5R 1206; low Digi-Key stock (123)",""
"C2,C40-C43,C62,C70-C74","100n","leo_control_box:C_0805_2012Metric","Samsung Electro-Mechanics","CL21B104KBCNNNC","1276-1003-1-ND","0.10","11","50 V X7R; used everywhere a 100 nF is needed",""
"C20-C25","peaking","leo_control_box:C_0805_2012Metric","","","","","6","DNP","DNP"
"D1","green","leo_control_box:LED_0805_2012Metric","Lite-On","LTST-C171GKT","160-1423-1-ND","0.15","1","green, used for both indicators",""
"D2","status","leo_control_box:LED_0805_2012Metric","Lite-On","LTST-C171GKT","160-1423-1-ND","0.15","1","green, used for both indicators",""
"F1","1.1A hold","leo_control_box:Fuse_1812_4532Metric","Littelfuse","1812L110/16DR","F3485CT-ND","0.74","1","replaces obsolete Bourns MF-MSMF110-2",""
"J3,J4","Qwiic","leo_control_box:JST_SH_SM04B-SRSS-TB_1x04-1MP_P1.00mm_Horizontal","JST","SM04B-SRSS-TB(LF)(SN)","455-SM04B-SRSS-TBCT-ND","0.51","2","",""
"J6","OBI sync","leo_control_box:PinHeader_1x04_P2.54mm_Vertical","Sullins","PRPC040SAAN-RC","S1011EC-40-ND","1.23","1","1x40 breakaway strip, cut for J6 and J11",""
"J9","DISPLAY","leo_control_box:IDC-Header_2x10_P2.54mm_Vertical","Sullins","SBH11-PBPC-D10-ST-BK","S9172-ND","0.46","1","2x10 shrouded box header for the display cable",""
"J10","USB-C 5V","leo_control_box:USB_C_Receptacle_GCT_USB4125-xx-x_6P_TopMnt_Horizontal","GCT","USB4125-GF-A","2073-USB4125-GF-ACT-ND","0.61","1","USB-C receptacle, power only (6 pin)",""
"J11","BUTTONS","leo_control_box:PinHeader_1x04_P2.54mm_Vertical","Sullins","PRPC040SAAN-RC","S1011EC-40-ND","1.23","1","1x40 breakaway strip, cut for J6 and J11",""
"Q1-Q6","NX3008NBK","leo_control_box:SOT-23","Nexperia","NX3008NBKVL","1727-NX3008NBKVLCT-ND","0.21","6","logic-level N-MOSFET, Vgs(th) <= 1.1 V, Ciss <= 50 pF; gate driven straight from the Teensy",""
"R1,R2,R30-R33,R73-R75","1k","leo_control_box:R_0805_2012Metric","Yageo","RC0805FR-071KL","311-1.00KCRCT-ND","0.10","9","",""
"R10-R15,R62-R64,R70-R72","10k","leo_control_box:R_0805_2012Metric","Yageo","RC0805FR-0710KL","311-10.0KCRCT-ND","0.10","12","",""
"R20-R25,R50,R51,R60,R61","56","leo_control_box:R_0805_2012Metric","Yageo","RC0805FR-0756RL","311-56.0CRCT-ND","0.10","10","",""
"R40,R41","2.2k","leo_control_box:R_0805_2012Metric","Yageo","RC0805FR-072K2L","311-2.20KCRCT-ND","0.10","2","",""
"R65,R66","5.1k","leo_control_box:R_0805_2012Metric","Yageo","RC0805FR-075K1L","311-5.10KCRCT-ND","0.10","2","USB-C CC pull-downs (sink, default USB power)",""
"U1","Teensy 4.0","leo_control_box:Teensy_4.0","PJRC / SparkFun","15583 (Teensy 4.0)","1568-15583-ND","25.66","1","owner has stock; Digi-Key stock 0 on 2026-11-13",""
"U4-U8,U12","HFBR-1521Z","leo_control_box:AGILENT_HFBR-152x","Broadcom","HFBR-1521Z","516-2043-ND","19.14","6","owner has stock; Digi-Key backordered (alt AFBR-1521CZ 516-3584-ND)",""
"U9-U11,U14","HFBR-2521Z","leo_control_box:AGILENT_HFBR-252x","Broadcom","HFBR-2521Z","516-2062-ND","20.46","4","owner has stock",""
"U13","ISO6720FBDR","leo_control_box:SOIC-8_3.9x4.9mm_P1.27mm","Texas Instruments","ISO6720FBDR","296-ISO6720FBDRCT-ND","2.13","1","2-ch digital isolator, outputs default low when unpowered",""
"X1","Display NHD-4.3","","Newhaven Display","NHD-4.3-800480FT-CSXP-CTP","757-NHD-4.3-800480FT-CSXP-CTP-ND","75.14","1","OFF-BOARD: 4.3 in 800x480 IPS EVE (FT813) display, capacitive touch",""
"X2","Display cable","","Adafruit","5294","1528-5294-ND","1.95","1","OFF-BOARD: 2x10 IDC socket-to-socket ribbon cable, 1 ft",""
"X3","Button red","","E-Switch","PS1024ALRED","EG2025-ND","1.76","1","OFF-BOARD: panel pushbutton, momentary, red (button 1, safe state)",""
"X4,X5","Button black","","E-Switch","PS1024ALBLK","EG2021-ND","1.66","2","OFF-BOARD: panel pushbutton, momentary, black (buttons 2 and 3)",""

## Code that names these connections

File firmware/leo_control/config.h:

// LEO 438VP control box firmware: board pins and build constants.
// Pin map follows hardware/leo_control_box (schematic rev 0.1).
#pragma once
#include <Arduino.h>

#define FW_NAME     "leo_control"
#define FW_VERSION  "0.1.0"
#define PROTO_VER   1

// Fiber UARTs (HFBR-1521Z TX through an NX3008 low-side switch: pin high = light on;
// HFBR-2521Z RX open collector: light on = pin LOW, so the receive side is normally inverted).
#define EHT_PORT    Serial1     // RX 0, TX 1
#define STG_PORT    Serial2     // RX 7, TX 8
#define VP_PORT     Serial3     // RX 15, TX 14

// EO board fibers
#define PIN_EO_F3   2           // register frames out (bit-banged, 3.6864 Mbit/s)
#define PIN_EO_F4   3           // read replies in
#define PIN_EO_F1   4           // frame gate out
#define PIN_EO_F2   5           // line gate out

// Isolated sync outputs to the OBI (ISO6720 side 1)
#define PIN_SYNC_LINE  6
#define PIN_SYNC_FRAME 9

// Display (FT813 EVE on SPI)
#define PIN_LCD_CS  10
#define PIN_LCD_PD  21
#define PIN_LCD_INT 22

// Front-panel buttons (active low) and status LED
#define PIN_BTN1    16
#define PIN_BTN2    17
#define PIN_BTN3    20
#define PIN_LED     23

// Qwiic I2C is on 18/19 (Wire); not used by this firmware yet.
